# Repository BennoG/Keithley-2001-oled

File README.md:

# Keithley-2001-oled

This is my attempt to put a OLED display in a Keithley 2001 - 2400 - 7000
This is for the almost unobtainable dot matrix VFD display.

At this moment only tested on a raspberry PI and raspberry PI pico
with a Keithley 2001 meter.

For the font I have added all the display test characters and also the bargrap characters.

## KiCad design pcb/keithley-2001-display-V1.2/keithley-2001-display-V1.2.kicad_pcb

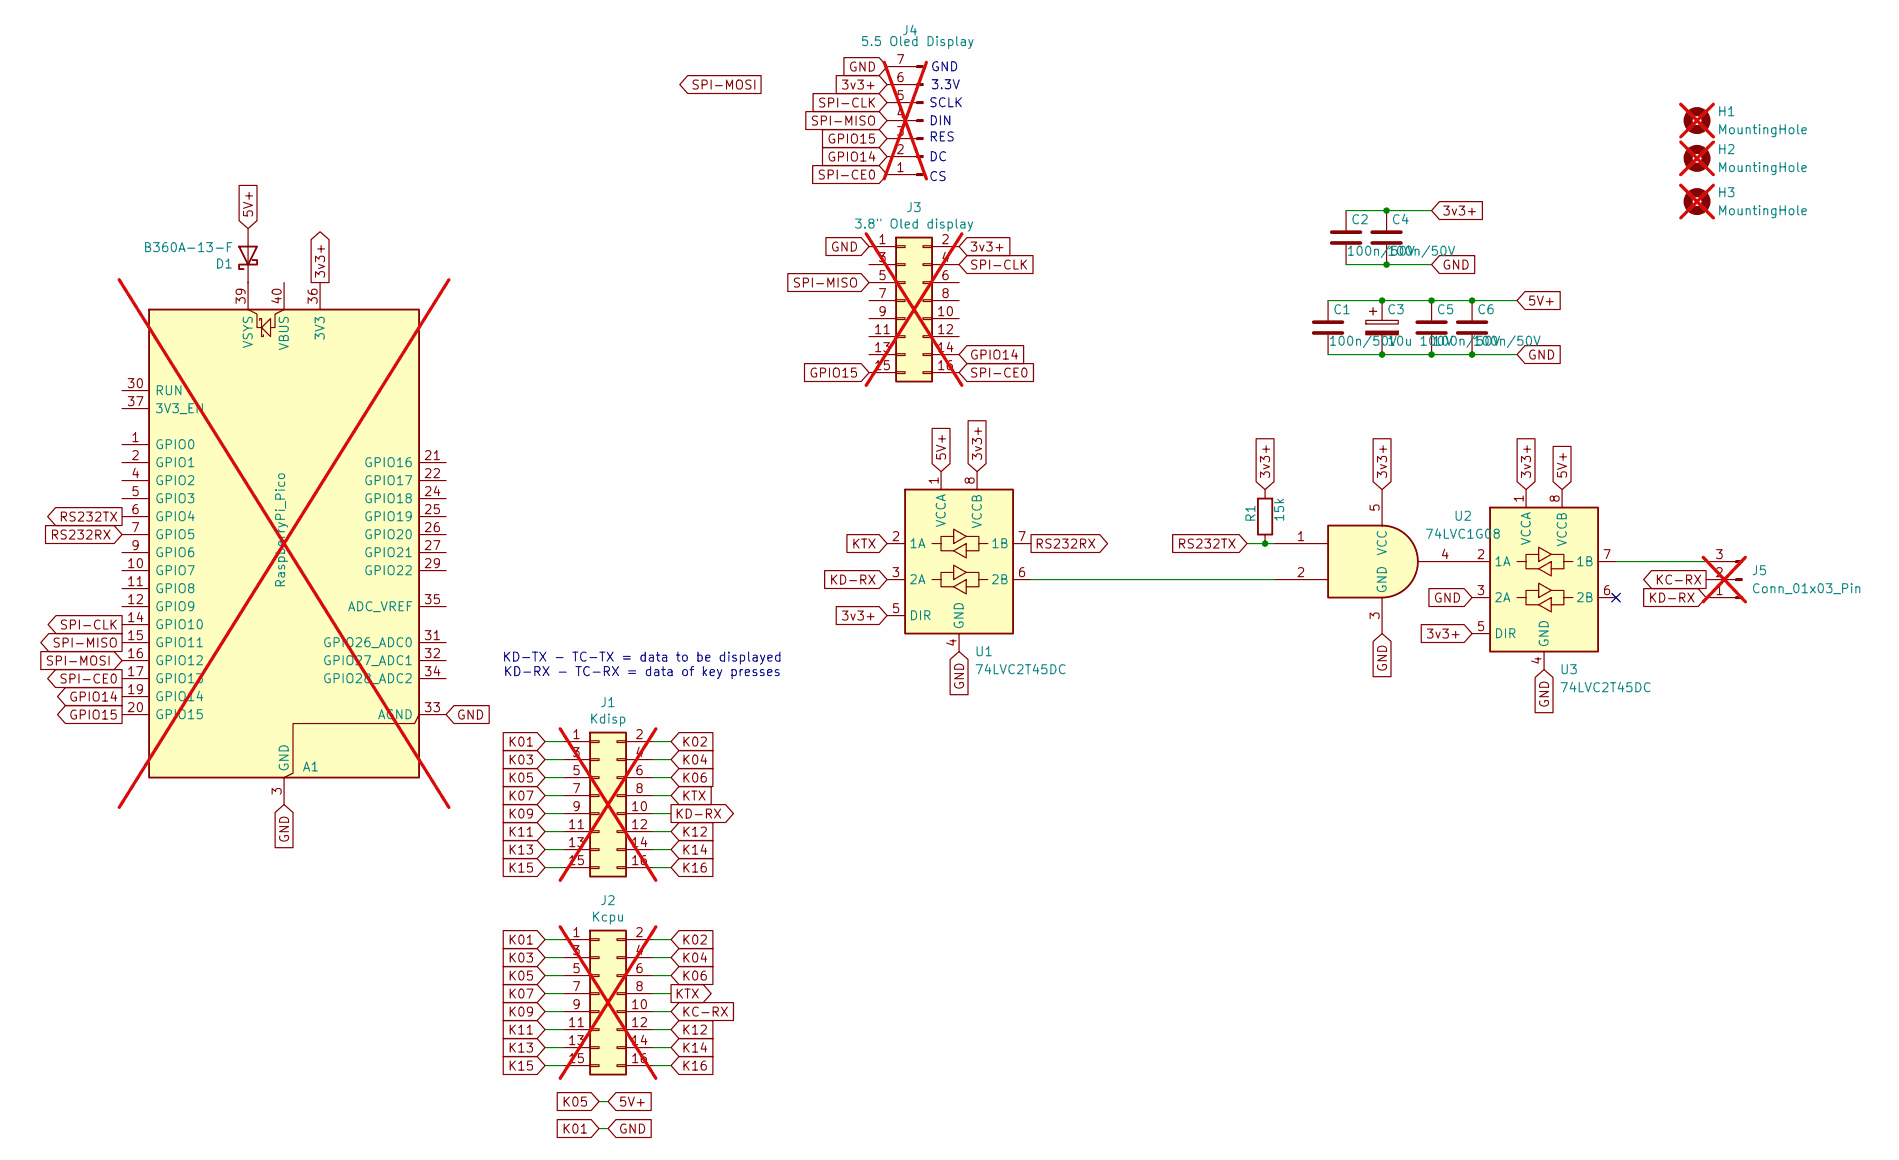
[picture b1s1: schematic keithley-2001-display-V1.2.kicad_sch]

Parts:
A1: RaspberryPi_Pico; RaspberryPi_Pico_Common_Unspecified; JLCPCB DNP; not fitted
C1, C2, C4, C5, C6: 100n/50V; C_0402_1005Metric; JLCPCB C307331
C3: 10u 100V; CP_Elec_8x6.2; JLCPCB C346985
D1: B360A-13-F; D_SMA; JLCPCB C14996
H1, H2, H3: MountingHole; MountingHole_2.7mm_M2.5; JLCPCB DNP; not fitted
J1: Kdisp; PinHeader_2x08_P2.54mm_Vertical; JLCPCB DNP; not fitted
J2: Kcpu; PinHeader_2x08_P2.54mm_Vertical; JLCPCB DNP; not fitted
J3: 3.8" Oled display; PinHeader_2x08_P2.54mm_Vertical; JLCPCB DNP; not fitted
J4: 5.5 Oled Display; PinHeader_1x07_P2.54mm_Vertical; JLCPCB DNP; not fitted
J5: Conn_01x03_Pin; PinHeader_1x03_P2.54mm_Vertical; JLCPCB DNP; not fitted
R1: 15k; R_0201_0603Metric; JLCPCB C22809
U1, U3: 74LVC2T45DC; VSSOP-8_2.3x2mm_P0.5mm; JLCPCB C15741
U2: 74LVC1G08; SOT-23-5; JLCPCB C7666

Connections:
3v3+: A1.36 (3V3), C2.1, C4.1, J3.2, J4.6, R1.2, U1.5 (DIR), U1.8 (VCCB), U2.5 (VCC), U3.1 (VCCA), U3.5 (DIR)
5V+: C1.1, C3.1, C5.1, C6.1, D1.2 (A), J1.5, J2.5, U1.1 (VCCA), U3.8 (VCCB)
GND: A1.3 (GND), A1.8 (GND), A1.13 (GND), A1.18 (GND), A1.23 (GND), A1.28 (GND), A1.33 (AGND), A1.38 (GND), C1.2, C2.2, C3.2, C4.2, C5.2, C6.2, J1.1, J2.1, J3.1, J4.7, U1.4 (GND), U2.3 (GND), U3.3 (2A), U3.4 (GND)
GPIO14: A1.19 (GPIO14), J3.14, J4.2
GPIO15: A1.20 (GPIO15), J3.15, J4.3
K02: J1.2, J2.2
K03: J1.3, J2.3
K04: J1.4, J2.4
K06: J1.6, J2.6
K07: J1.7, J2.7
K09: J1.9, J2.9
K11: J1.11, J2.11
K12: J1.12, J2.12
K13: J1.13, J2.13
K14: J1.14, J2.14
K15: J1.15, J2.15
K16: J1.16, J2.16
KC-RX: J2.10, J5.2
KD-RX: J1.10, J5.1, U1.3 (2A)
KTX: J1.8, J2.8, U1.2 (1A)
unnamed: A1.39 (VSYS), D1.1 (K)
unnamed: J5.3, U3.7 (1B)
unnamed: U1.6 (2B), U2.2
unnamed: U2.4, U3.2 (1A)
RS232RX: A1.7 (GPIO5), U1.7 (1B)
RS232TX: A1.6 (GPIO4), R1.1, U2.1
SPI-CE0: A1.17 (GPIO13), J3.16, J4.1
SPI-CLK: A1.14 (GPIO10), J3.4, J4.5
SPI-MISO: A1.15 (GPIO11), J3.5, J4.4
SPI-MOSI: A1.16 (GPIO12)

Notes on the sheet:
RES
3.3V
SCLK
GND
KD-TX - TC-TX = data to be displayed KD-RX - TC-RX = data of key presses
DIN

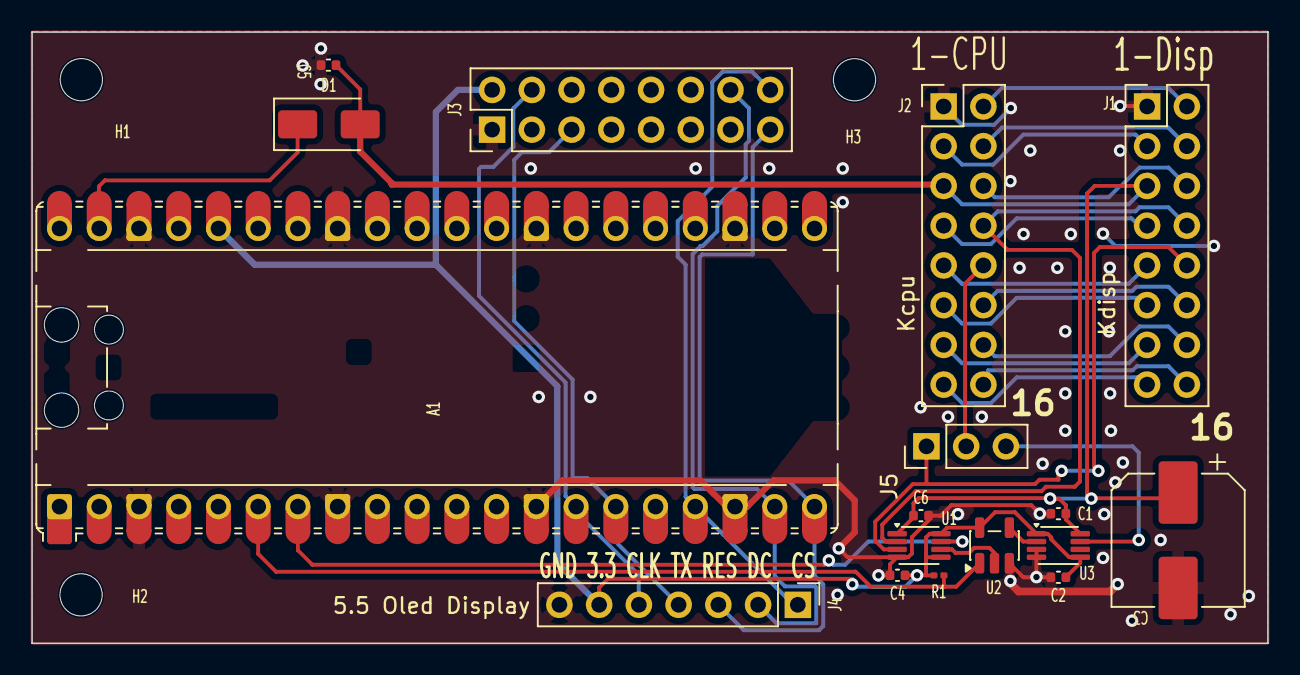
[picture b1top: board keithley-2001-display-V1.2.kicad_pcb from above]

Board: 2 copper layers, 79.0 x 39.1 mm, 20 parts (0 on the bottom side), 29 nets.

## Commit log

2026-06-03 first upload
2026-06-03 added pcb and wiring diagrams
2026-06-03 Gerber files added for this PCB
2026-06-03 added image of the results with 3.8" display
    Added an image to the README for better visualization.
2026-06-04 Working with Keithlely 7001 Stop flashing display for empty data strings option to log last 5000 bytes to console "dump<CR>" option to return to boot update mode "boot<CR>" or "F1" key
2026-06-05 Celsius and Omega character added. Tested on 5.5"display working but need nicer font for the big numbers
2026-06-05 Front panel identification for if used as complete replacement Also key definitions documented in code for the K2001
2026-06-10 compatible with K2000 (not all border bits found)
2026-06-16 Added some basic kind of anti aliassing for the big fonts. Provided for a special character remapping and font file. K2000 and K2001 compatible (not yet figured out how to auto detect) Command line i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
